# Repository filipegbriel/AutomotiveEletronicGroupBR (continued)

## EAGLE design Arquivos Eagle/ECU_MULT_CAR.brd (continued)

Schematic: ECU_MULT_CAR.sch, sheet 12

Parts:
BORBOLETA_1, BORBOLETA_2: PINO_TORNEADO
C38: 33nF; C0805
C40, C115: 100nF; C0805
C95: 47uF/25V; E2,5-7
PIN: CONCTOR_BOSCH; V23542-A1280-B300
R41: 10K; M0805
U$3: MC33186; HSOP-20-PIN

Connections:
+5V: R41.1; also elsewhere on the board
BORBOLETA_PIN_66: BORBOLETA_2.1, PIN.66, U$3.14 (OUT2), U$3.15 (OUT2_2)
BORBOLETA_PIN_80: BORBOLETA_1.1, PIN.80, U$3.6 (OUT1), U$3.7 (OUT1_2)
GND3: U$3.1 (AGND); also elsewhere on the board
IGND: C38.2, C40.2, C95.-, C115.2, PIN.28, U$3.10 (PGND_2), U$3.11 (PGND_3), U$3.12 (PGND_4), U$3.21A (EPAD); also elsewhere on the board
LINHA_15_PIN27: C40.1, C95.+, C115.1, U$3.4 (VBAT), U$3.5 (VBAT_2), U$3.16 (VBAT_3); also elsewhere on the board
unnamed: C38.1, U$3.17 (CP)
RA3_ADMISS_DI2__BORBO: U$3.13 (DI2); also elsewhere on the board
RB1_ADMISS_DI1_BORBO: U$3.18 (DI1); also elsewhere on the board
RB2_ADMISS_COD_BORBO: U$3.8 (COD); also elsewhere on the board
RB3_ADMISS_IN1_BORBO: U$3.3 (IN1); also elsewhere on the board
RB4_ADMISS_SF_BORBO: R41.2, U$3.2 (SF); also elsewhere on the board
RB5_ADMISS_IN2_BORBO: U$3.19 (IN2); also elsewhere on the board

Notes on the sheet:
Controle da Válvula Borboleta
Circuito Admissão
FACULDADE DE TECNOLOGIA DE SANTO ANDRÉ Rua Prefeito Justino Paixão, 150 - Centro Santo André - SP - CEP:09020-130 (11) 4437-2216
MARK 1

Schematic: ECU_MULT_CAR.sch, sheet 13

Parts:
C25, C26, C27, C28, C29, C30, C31, C32, C107, C108: 100nF; C0805
D5, D6, D14, D15: 1n4148; MINIMELF
IC6, IC7: LM358D; SO08
PIN: CONCTOR_BOSCH; V23542-A1280-B300
R25, R26, R27, R28, R29, R30: 10K; M0805
RA0_ADMISS_TPS_1, RA1_ADMISS_TPS_2: PINO_TORNEADO
TPS_1_IN, TPS_2_IN: PINO_TORNEADO

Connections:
+5V: D5.C, D6.C, D14.C, D15.C; also elsewhere on the board
GND3: C25.1, C27.1, C28.2, C29.2, C30.1, C32.1, C107.1, C108.2, IC6.4 (V-), IC7.4 (V-); also elsewhere on the board
unnamed: C107.2, D5.A, IC6.3 (+IN), R25.2
unnamed: IC6.1 (OUT), IC6.2 (-IN), R26.1
unnamed: C26.1, R26.2, R27.1
unnamed: C27.2, IC6.5 (+IN), R27.2
unnamed: C29.1, D6.A, IC7.3 (+IN), R28.2
unnamed: IC7.1 (OUT), IC7.2 (-IN), R29.1
unnamed: C31.1, R29.2, R30.1
unnamed: C32.2, IC7.5 (+IN), R30.2
RA0_ADMISS_TPS_1: C26.2, C28.1, D14.A, IC6.6 (-IN), IC6.7 (OUT), RA0_ADMISS_TPS_1.1; also elsewhere on the board
RA1_ADMISS_TPS_2: C31.2, C108.1, D15.A, IC7.6 (-IN), IC7.7 (OUT), RA1_ADMISS_TPS_2.1; also elsewhere on the board
TPS1_PIN_75: PIN.75, R25.1, TPS_1_IN.1
TPS2_PIN_68: PIN.68, R28.1, TPS_2_IN.1
V+: C25.2, C30.2, IC6.8 (V+), IC7.8 (V+); also elsewhere on the board

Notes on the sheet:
Circuito Condicionador Analógico Admissão
TPS_1
TPS_2
FACULDADE DE TECNOLOGIA DE SANTO ANDRÉ Rua Prefeito Justino Paixão, 150 - Centro Santo André - SP - CEP:09020-130 (11) 4437-2216
MARK 1

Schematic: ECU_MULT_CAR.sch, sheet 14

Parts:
BOB1, BOB2: LEDKA-3528ASYC; KA-3528ASYC
C39: 100uF/16V; E2,5-7
C72, C93, C100: 100pF; C0805
C89, C90: 22pF; C0805
JP3: JP3Q
LED3: LEDKA-3528ASYC; KA-3528ASYC
PIN: CONCTOR_BOSCH; V23542-A1280-B300
Q3: 10Mhz; SM49
R110, R146, R147: 1K; M0805
R116: 470R; M0805
R117: 10K; M0805
R145: 1M; M0805
S6: 10-XX; B3F-10XX
SINCRONISMO: PIC18F44K22; DIP40
SV2: MA03-1
X4, X6: MKDSN1,5/3-5,08

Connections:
+5V: C39.+, C72.1, C93.1, R110.2, R117.1, SINCRONISMO.11 (VCC), SINCRONISMO.32 (VCC_1); also elsewhere on the board
DGND: BOB1.C, BOB2.C, C39.-, C72.2, C89.1, C90.1, C93.2, C100.2, JP3.5, S6.1 (S), S6.2 (S1), SINCRONISMO.12 (GND), SINCRONISMO.31 (GND_1); also elsewhere on the board
ED_PIN_57: PIN.57, R147.1, SINCRONISMO.15 (RC0/P2B/T3CKI/T3G/T1CKI/SOSCO)
ED_PIN_71: PIN.71, R146.1, SINCRONISMO.16 (RC1/P2A/CCP2/SOSCI)
LINHA15: SINCRONISMO.34 (RB1/INT1/C12IN3-/AN10); also elsewhere on the board
unnamed: BOB1.A, R146.2
unnamed: BOB2.A, R147.2
unnamed: C89.2, Q3.1, R145.2, SINCRONISMO.13 (RA7/CLKI/OSC1)
unnamed: SINCRONISMO.2 (RA0/C12IN0-/ANO), X4.1
unnamed: LED3.A, R110.1
unnamed: C90.2, Q3.2, R145.1, SINCRONISMO.14 (RA6/CLKO/OSC2)
unnamed: LED3.C, SINCRONISMO.4 (RA2/C2IN+/AN2/DACOUT/VREF-), X6.2
unnamed: R116.2, SINCRONISMO.1 (~MCLR/VPP/RE3)
unnamed: C100.1, JP3.1, R116.1, R117.2, S6.3, S6.4 (P1)
unnamed: JP3.2, SINCRONISMO.40 (RB7/IOC3/PGD)
unnamed: JP3.3, SINCRONISMO.39 (RB6/IOC2/PGC)
unnamed: SINCRONISMO.3 (RA1/C12IN1-/AN1), X6.3
unnamed: SINCRONISMO.5 (RA3/C1IN+/AN3/VREF+), X6.1
RA4_SINCRO_BOM_PART_FRIA: SINCRONISMO.6 (RA4/C1OUT/SRQ/TOCKI); also elsewhere on the board
RB0_SINCRO_SELEC_ROTACAO_1: SINCRONISMO.33 (RB0/INT0/FLT0/SRI/AN12), SV2.1
RB0_SINCRO_SELEC_ROTACAO_2: SINCRONISMO.38 (RB5/IOC1/P3A/CCP3/T3CKI/T1G/AN13), SV2.3
RB2_SINCRO_INJ_PART_FRIA: SINCRONISMO.35 (RB2/INT32/CTED1/AN8); also elsewhere on the board
RB3_SINCRO_VENT_VEL_1: SINCRONISMO.36 (RB3/CTED2/P2A/CCP2/C12IN2-/AN9); also elsewhere on the board
RB4_SINCRO_VENT_VEL_2: SINCRONISMO.37 (RB4/IOC0/TG5/AN11); also elsewhere on the board
RC2_SINCRO_RELE_AR_COND: SINCRONISMO.17 (RC2/CTPLS/P1A/CCP1/T5CKI/AN14); also elsewhere on the board
RC6_GERENCI_RA5_CS_SINCRON: SINCRONISMO.7 (RA5/C2OUT/SRNQ/~SS1/HLVDIN/AN4); also elsewhere on the board
RC6_SINCRO_MAXI_IGN/INJ: SINCRONISMO.25 (RC6/TX1/CK1/AN18); also elsewhere on the board
RC7_SINCRO_NOMI_IGN/INJ: SINCRONISMO.26 (RC7/RX1/DT1/AN19); also elsewhere on the board
RD0_SINCRO_DIN0_IGN/INJ: SINCRONISMO.21 (RD2/P2B/AN22); also elsewhere on the board
RD1_SINCRO_DIN1_IGN/INJ: SINCRONISMO.22 (RD3/P2C/~SS2/AN23); also elsewhere on the board
RD2_SINCRO_DIN2_IGN/INJ: SINCRONISMO.19 (RD0/SCK2/SCL2/AN20); also elsewhere on the board
RD3_SINCRO_DIN3_IGN/INJ: SINCRONISMO.20 (RD1/CCP4/SDI2/SDA2/AN21); also elsewhere on the board
RD4_SINCRO_GIN0_IGN/INJ: SINCRONISMO.27 (RD4/P2D/SDO2/AN24); also elsewhere on the board
RD5_SINCRO_GIN1_IGN/INJ: SINCRONISMO.28 (RD5/P1B/AN25); also elsewhere on the board
RD6_SINCRO_GIN2_IGN/INJ: SINCRONISMO.29 (RD6/P1C/TX2/CK2/AN26); also elsewhere on the board
RD7_SINCRO_GIN3_IGN/INJ: SINCRONISMO.30 (RD7/P1D/RX2/DT2/AN27); also elsewhere on the board
RE0_SINCRO_OUT_EN_IGN/INJ: SINCRONISMO.8 (RE0/P3A/CCP3/AN5); also elsewhere on the board
RE1_SINCRO_SPK_IGN/INJ: SINCRONISMO.9 (RE1/P3B/AN6); also elsewhere on the board
RE2_SINCRO_FASE: SINCRONISMO.10 (RE2/CCP5/AN7); also elsewhere on the board
ROTAÇÃO: SV2.2; also elsewhere on the board
SCK1_GERENC: SINCRONISMO.18 (RC3/SCK1/SCL1/AN15); also elsewhere on the board
SDI1_GERENC: SINCRONISMO.24 (RC5/SDO1/AN17); also elsewhere on the board
SDO1_GERENC: SINCRONISMO.23 (RC4/SDI1/SDA1/AN16); also elsewhere on the board
SENSOR_COMBUSTIVEL: X4.2; also elsewhere on the board
SENSOR_VELOCIDADE: X4.3; also elsewhere on the board

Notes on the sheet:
PIC Sincronismo
FACULDADE DE TECNOLOGIA DE SANTO ANDRÉ Rua Prefeito Justino Paixão, 150 - Centro Santo André - SP - CEP:09020-130 (11) 4437-2216
MARK 1

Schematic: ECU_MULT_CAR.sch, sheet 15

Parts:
C41, C46, C47, C48, C49, C50, C62: 100nF; C0805
IGN1, IGN2, IGN3, IGN4: LEDKA-3528ASYC; KA-3528ASYC
INJ1, INJ2, INJ3, INJ4: LEDKA-3528ASYC; KA-3528ASYC
MC1: MC33810; SOIC_32_PIN
PIN: CONCTOR_BOSCH; V23542-A1280-B300
R42, R49, R50, R51: 36k/1W; R2512
R52, R53: 100R; M0805
R54: 0R02; M0805
R55, R56, R57, R58: 4K; M0805
R119, R120, R121, R122, R123, R124, R125, R126: 1K; M0805
R127, R128: 10K; M0805
U$4, U$6, U$7, U$8: IRGS14C40L; TO-263AB
X5: MKDSN1,5/4-5,08

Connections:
+5V: C48.1, MC1.8 (VDD), R127.2, R128.2; also elsewhere on the board
BOBINA_1: C41.1, R42.2, U$4.SOURCE (DRAIN), X5.1
BOBINA_2: C47.1, R49.2, U$6.SOURCE (DRAIN), X5.2
BOBINA_3: C46.1, R50.2, U$7.SOURCE (DRAIN), X5.3
BOBINA_4: C49.1, R51.2, U$8.SOURCE (DRAIN), X5.4
DGND: C48.2, C50.2, IGN1.C, IGN2.C, IGN3.C, IGN4.C, INJ1.C, INJ2.C, INJ3.C, INJ4.C; also elsewhere on the board
IGND: C62.2, MC1.33 (GND), R53.2, R54.1, R55.2, R56.2, R57.2, R58.2; also elsewhere on the board
INJETOR_1_PIN_79: MC1.1 (OUT0), PIN.79
INJETOR_2_PIN_59: MC1.16 (OUT1), PIN.59
INJETOR_3_PIN_73: MC1.32 (OUT2), PIN.73
INJETOR_4_PIN_65: MC1.17 (OUT3), PIN.65
unnamed: C41.2, MC1.2 (FB0), R42.1, R55.1
unnamed: C47.2, MC1.15 (FB1), R49.1, R56.1
unnamed: C46.2, MC1.31 (FB2), R50.1, R57.1
unnamed: C49.2, MC1.18 (FB3), R51.1, R58.1
unnamed: C62.1, R52.2, R54.2, U$4.DRAIN (SOURCE), U$6.DRAIN (SOURCE), U$7.DRAIN (SOURCE), U$8.DRAIN (SOURCE)
unnamed: MC1.3 (GD0), U$4.GATE
unnamed: MC1.14 (GD1), U$6.GATE
unnamed: MC1.30 (GD2), U$7.GATE
unnamed: MC1.19 (GD3), U$8.GATE
unnamed: MC1.26 (RSP), R52.1
unnamed: MC1.27 (RSN), R53.1
unnamed: INJ1.A, R119.2
unnamed: INJ2.A, R120.2
unnamed: INJ3.A, R121.2
unnamed: INJ4.A, R122.2
unnamed: IGN1.A, R123.2
unnamed: IGN2.A, R124.2
unnamed: IGN3.A, R125.2
unnamed: IGN4.A, R126.2
RC1_GERENC_CS_INJ/IGN: MC1.4 (/CS); also elsewhere on the board
RC6_SINCRO_MAXI_IGN/INJ: MC1.29 (MAXI); also elsewhere on the board
RC7_SINCRO_NOMI_IGN/INJ: MC1.28 (NOMI); also elsewhere on the board
RD0_SINCRO_DIN0_IGN/INJ: MC1.10 (DIN0), R119.1; also elsewhere on the board
RD1_SINCRO_DIN1_IGN/INJ: MC1.11 (DIN1), R120.1; also elsewhere on the board
RD2_SINCRO_DIN2_IGN/INJ: MC1.12 (DIN2), R121.1; also elsewhere on the board
RD3_SINCRO_DIN3_IGN/INJ: MC1.13 (DIN3), R122.1; also elsewhere on the board
RD4_SINCRO_GIN0_IGN/INJ: MC1.24 (GIN0), R123.1; also elsewhere on the board
RD5_SINCRO_GIN1_IGN/INJ: MC1.23 (GIN1), R124.1; also elsewhere on the board
RD6_SINCRO_GIN2_IGN/INJ: MC1.22 (GIN2), R125.1; also elsewhere on the board
RD7_SINCRO_GIN3_IGN/INJ: MC1.21 (GIN3), R126.1; also elsewhere on the board
RE0_SINCRO_OUT_EN_IGN/INJ: MC1.9 (/OUT_EN), R127.1; also elsewhere on the board
RE1_SINCRO_SPK_IGN/INJ: MC1.20 (/SPKDUR), R128.1; also elsewhere on the board
SCK1_GERENC: MC1.5 (SCLK); also elsewhere on the board
SDI1_GERENC: MC1.7 (SO); also elsewhere on the board
SDO1_GERENC: MC1.6 (SI); also elsewhere on the board
V+: C50.1, MC1.25 (VPWR); also elsewhere on the board

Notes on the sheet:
Condicionador Digital Injeção/Ignição Sincronismo
FACULDADE DE TECNOLOGIA DE SANTO ANDRÉ Rua Prefeito Justino Paixão, 150 - Centro Santo André - SP - CEP:09020-130 (11) 4437-2216
MARK 1

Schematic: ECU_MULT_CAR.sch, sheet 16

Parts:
ANTER_IN: PINO_TORNEADO
C5, C6, C7, C8, C109, C116, C117, C118, C120, C121: 100nF; C0805
D2, D16, D21, D22: 1n4148; MINIMELF
IC2, IC9: LM358D; SO08
MAP_IN: PINO_TORNEADO
MAP_OUT: PINO_TORNEADO
PIN: CONCTOR_BOSCH; V23542-A1280-B300
R5, R6, R7, R158, R159: 10K; M0805
R157: 3K6; M0805
R160: 1K; M0805
RA2_ADMISS_ALTERNADOR: PINO_TORNEADO
S2: 2P2T

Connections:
+5V: D2.C, D16.C, D21.C, D22.C; also elsewhere on the board
GND3: C5.2, C6.2, C8.2, C109.2, C117.2, C118.2, C120.1, C121.1, IC2.4 (V-), IC9.4 (V-), R160.1; also elsewhere on the board
MAP_PIN10: PIN.10, S2.3.1, S2.3.2
MAP_PIN70: PIN.70, S2.1.1, S2.1.2
unnamed: C109.1, D2.A, IC2.3 (+IN), R5.2
unnamed: IC2.1 (OUT), IC2.2 (-IN), R6.1
unnamed: C7.2, R6.2, R7.1
unnamed: C6.1, IC2.5 (+IN), R7.2
unnamed: MAP_IN.1, R5.1, S2.2.1, S2.2.2
unnamed: ANTER_IN.1, PIN.11, R157.1
unnamed: C117.1, D21.A, IC9.3 (+IN), R157.2, R160.2
unnamed: IC9.1 (OUT), IC9.2 (-IN), R158.1
unnamed: C116.1, R158.2, R159.1
unnamed: C120.2, IC9.5 (+IN), R159.2
RA2_ADMISS_ALTERNADOR: C116.2, C121.2, D22.A, IC9.6 (-IN), IC9.7 (OUT), RA2_ADMISS_ALTERNADOR.1; also elsewhere on the board
RE0_GERENC_MAP: C5.1, C7.1, D16.A, IC2.6 (-IN), IC2.7 (OUT), MAP_OUT.1; also elsewhere on the board
V+: C8.1, C118.1, IC2.8 (V+), IC9.8 (V+); also elsewhere on the board

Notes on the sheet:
MAP
Alternador
Condicionador Analógico
FACULDADE DE TECNOLOGIA DE SANTO ANDRÉ Rua Prefeito Justino Paixão, 150 - Centro Santo André - SP - CEP:09020-130 (11) 4437-2216
MARK 1

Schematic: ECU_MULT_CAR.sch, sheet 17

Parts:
C42, C43, C57, C61, C75, C76, C105, C106: 100nF; C0805
LED4: LEDKA-3528ASYC; KA-3528ASYC
LINHA15: PINO_TORNEADO
LINHA_15_IN: PINO_TORNEADO
MEDI_VELO_IN: PINO_TORNEADO
MEDI_VELO_OUT: PINO_TORNEADO
PIN: CONCTOR_BOSCH; V23542-A1280-B300
R31, R45, R70, R92: 5K6; M0805
R43, R44, R71, R72, R85, R86, R87, R88, R91, R93, R129, R130, R135, R136, R141, R142: 10K; M0805
R111: 1K; M0805
RD2_GERENC_FREIO_1: PINO_TORNEADO
RE2_SINCRO_FASE: PINO_TORNEADO
S1: 2P2T
SENSOR_FASE_IN: PINO_TORNEADO
SENSOR_IN1: PINO_TORNEADO
U1, U3: LM339; SOIC14N

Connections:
+5V: C42.1, C43.1, C61.1, C76.1, R43.1, R44.1, R72.1, R85.1, R86.1, R87.1, R91.1, R129.1, R135.1, R141.1, U1.3 (V+); also elsewhere on the board
DGND: C42.2, C43.2, C57.2, C61.2, C75.2, C76.2, C105.2, C106.2, LED4.C, R31.2, R45.2, R70.2, R88.2, R92.2, R130.2, R136.2, R142.2, U1.12 (V-); also elsewhere on the board
LINHA15: LINHA15.1, R91.2, U1.1 (OUT); also elsewhere on the board
LINHA_15_PIN4: PIN.4, S1.1.1, S1.1.2
LINHA_15_PIN27: PIN.27, S1.3.1, S1.3.2; also elsewhere on the board
unnamed: R87.2, R88.1, U3.10 (-IN)
unnamed: R70.1, R71.2, U3.5 (+IN)
unnamed: C57.1, PIN.23, R71.1, SENSOR_IN1.1
unnamed: R129.2, R130.1, U3.4 (-IN)
unnamed: R92.1, R93.2, U1.7 (+IN)
unnamed: LED4.A, R111.1
unnamed: C75.1, LINHA_15_IN.1, R93.1, R111.2, S1.2.1, S1.2.2
unnamed: C106.1, PIN.60, R44.2, R45.1, SENSOR_FASE_IN.1, U3.9 (+IN)
unnamed: R135.2, R136.1, U3.8 (-IN)
unnamed: R141.2, R142.1, U1.6 (-IN)
RD1_ADMISS_VELOCIDA: MEDI_VELO_OUT.1, R86.2, U3.13 (OUT); also elsewhere on the board
RD2_GERENC_FREIO_1: R72.2, RD2_GERENC_FREIO_1.1, U3.2 (OUT); also elsewhere on the board
RE2_SINCRO_FASE: R43.2, RE2_SINCRO_FASE.1, U3.14 (OUT); also elsewhere on the board
SENSOR_VELOCIDADE: C105.1, MEDI_VELO_IN.1, PIN.5, R31.1, R85.2, U3.11 (+IN); also elsewhere on the board

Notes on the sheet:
Fase
Freio 1
Linha 15
Velocidade
Condicionador Digital
FACULDADE DE TECNOLOGIA DE SANTO ANDRÉ Rua Prefeito Justino Paixão, 150 - Centro Santo André - SP - CEP:09020-130 (11) 4437-2216
MARK 1

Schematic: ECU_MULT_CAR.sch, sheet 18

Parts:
C33: 330nF; C0805
C34: 47nF; C0805
C35: 1nF; C0805
C36, C37: 100nF; C0805
OP.MODE: M251
PIN: CONCTOR_BOSCH; V23542-A1280-B300
R33: 100K; M0805
R34: 1K; M0805
R35: 150K; M0805
R36, R39: 5K6; M0805
R37: 18K; M0805
R38, R40, R143, R144, R170: 10K; M0805
RELUTÂNCIA: PINO_TORNEADO
ROT_ANAL: PINO_TORNEADO
ROT_DIG_IN: PINO_TORNEADO
ROT_DIG_OUT: PINO_TORNEADO
SENSIBILIDADE: M251
SV3: MA04-2
U3: LM339; SOIC14N
U$2: LM1815; SOICLM1815

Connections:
+5V: C37.1, R35.1, R36.1, R38.1, R143.1, R170.1, SENSIBILIDADE.1 (O), U3.3 (V+), U$2.8 (VCC); also elsewhere on the board
DGND: C33.2, C34.2, C35.1, C36.2, C37.2, OP.MODE.3 (S), R33.1, R34.1, R39.2, R144.2, SENSIBILIDADE.3 (S), U3.12 (V-), U$2.2 (GND); also elsewhere on the board
ENTRADA_DIGITAL_PIN_53: PIN.53, SV3.2, SV3.8
unnamed: C33.1, R33.2, U$2.7 (PEAK)
unnamed: R37.1, U$2.3 (VIN)
unnamed: R34.2, U$2.10 (GATED)
unnamed: C35.2, OP.MODE.2, R35.2, U$2.14 (RC_TIMING)
unnamed: R39.1, R40.2, U3.7 (+IN)
unnamed: C36.1, R40.1, R170.2, ROT_DIG_IN.1, SV3.1
unnamed: SENSIBILIDADE.2, U$2.5 (MODE)
unnamed: R143.2, R144.1, U3.6 (-IN)
RELUTÂNCIA: C34.1, R37.2, RELUTÂNCIA.1, SV3.7
ROTAÇÃO: SV3.3, SV3.5; also elsewhere on the board
ROT_ANA: R36.2, ROT_ANAL.1, SV3.6, U$2.12 (PULSE_OUT)
ROT_DIG: R38.2, ROT_DIG_OUT.1, SV3.4, U3.1 (OUT)

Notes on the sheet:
Condicionador Analógico/Digital Rotação
FACULDADE DE TECNOLOGIA DE SANTO ANDRÉ Rua Prefeito Justino Paixão, 150 - Centro Santo André - SP - CEP:09020-130 (11) 4437-2216
MARK 1

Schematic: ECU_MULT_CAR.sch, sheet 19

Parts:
PIN: CONCTOR_BOSCH; V23542-A1280-B300
R32, R106, R155: 1K; M0805
R94, R96, R98, R100, R102, R148, R149, R150, R151: 100k; M0805
R95, R97, R99, R101, R103: 1k; M0805
R153: 220R; M0805
U$1, U$13, U$16, U$17, U$26, U$27, U$28, U$29, U$30: IRLL014N; SOT-223

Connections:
AQUECE_SONDA_PIN13: PIN.13, U$1.2 (D), U$1.4 (D)
AQUECE_SONDA_PIN_1: PIN.1, U$16.2 (D), U$16.4 (D)
BOMBA_PARTIDA_FRIO_PIN48: PIN.48, U$27.2 (D), U$27.4 (D)
CARVAO_ATIVO_PIN14: PIN.14, U$13.2 (D), U$13.4 (D)
DGND: R94.1, R96.1, R98.1, R100.1, R102.1, R148.1, R149.1, R150.1, R151.1, U$1.3 (S), U$13.3 (S), U$16.3 (S), U$17.3 (S), U$26.3 (S), U$27.3 (S), U$28.3 (S), U$29.3 (S), U$30.3 (S); also elsewhere on the board
INJETOR_PART_FRIO_PIN_64: PIN.64, U$26.2 (D), U$26.4 (D)
unnamed: R95.1, R98.2, U$16.1 (G)
unnamed: R96.2, R97.1, U$1.1 (G)
unnamed: R94.2, R99.1, U$13.1 (G)
unnamed: R100.2, R103.1, U$17.1 (G)
unnamed: R32.1, R148.2, U$26.1 (G)
unnamed: R106.1, R149.2, U$27.1 (G)
unnamed: R101.1, R102.2, U$30.1 (G)
unnamed: R150.2, R153.1, U$29.1 (G)
unnamed: R151.2, R155.1, U$28.1 (G)
RA4_SINCRO_BOM_PART_FRIA: R106.2; also elsewhere on the board
RB2_SINCRO_INJ_PART_FRIA: R32.2; also elsewhere on the board
RB3_SINCRO_VENT_VEL_1: R153.2; also elsewhere on the board
RB4_SINCRO_VENT_VEL_2: R101.2; also elsewhere on the board
RC2_SINCRO_RELE_AR_COND: R155.2; also elsewhere on the board
RD6_ADMISS_AQUEC_SONDA_1: R95.2; also elsewhere on the board
RD7_ADMISS_AQUEC_SONDA_2: R97.2; also elsewhere on the board
RD7_GERENC_BOMB_INJ: R103.2; also elsewhere on the board
RE2_ADMISS_CARVãO: R99.2; also elsewhere on the board
RELE_AR_CONDICIONADO_PIN42: PIN.42, U$28.2 (D), U$28.4 (D)
RELÉ5_BOMBA_INJET_PIN26: PIN.26, U$17.2 (D), U$17.4 (D)
VENTILADOR_VEL_1_PIN22: PIN.22, U$29.2 (D), U$29.4 (D)
VENTILADOR_VEL_2_PIN40: PIN.40, U$30.2 (D), U$30.4 (D)

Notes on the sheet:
Circuitos Condicionadores de Acionamento de Relés
FACULDADE DE TECNOLOGIA DE SANTO ANDRÉ Rua Prefeito Justino Paixão, 150 - Centro Santo André - SP - CEP:09020-130 (11) 4437-2216
MARK 1

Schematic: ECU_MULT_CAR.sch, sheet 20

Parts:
PIN: CONCTOR_BOSCH; V23542-A1280-B300

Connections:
+5V: PIN.6, PIN.8, PIN.55, PIN.62; also elsewhere on the board
+VBAT: PIN.15; also elsewhere on the board
DGND: PIN.2, PIN.67; also elsewhere on the board
GND3: PIN.7, PIN.19, PIN.54, PIN.61; also elsewhere on the board

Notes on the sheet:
Referência Negativa Analógica
Referência Negativa Ignição
Referência Negativa Digital
Pinos que não foram usados
Alimentação 12 Volts Bateria do Veiculo
Alimentação 5 Volts retificada
Informações
FACULDADE DE TECNOLOGIA DE SANTO ANDRÉ Rua Prefeito Justino Paixão, 150 - Centro Santo André - SP - CEP:09020-130 (11) 4437-2216
MARK 1

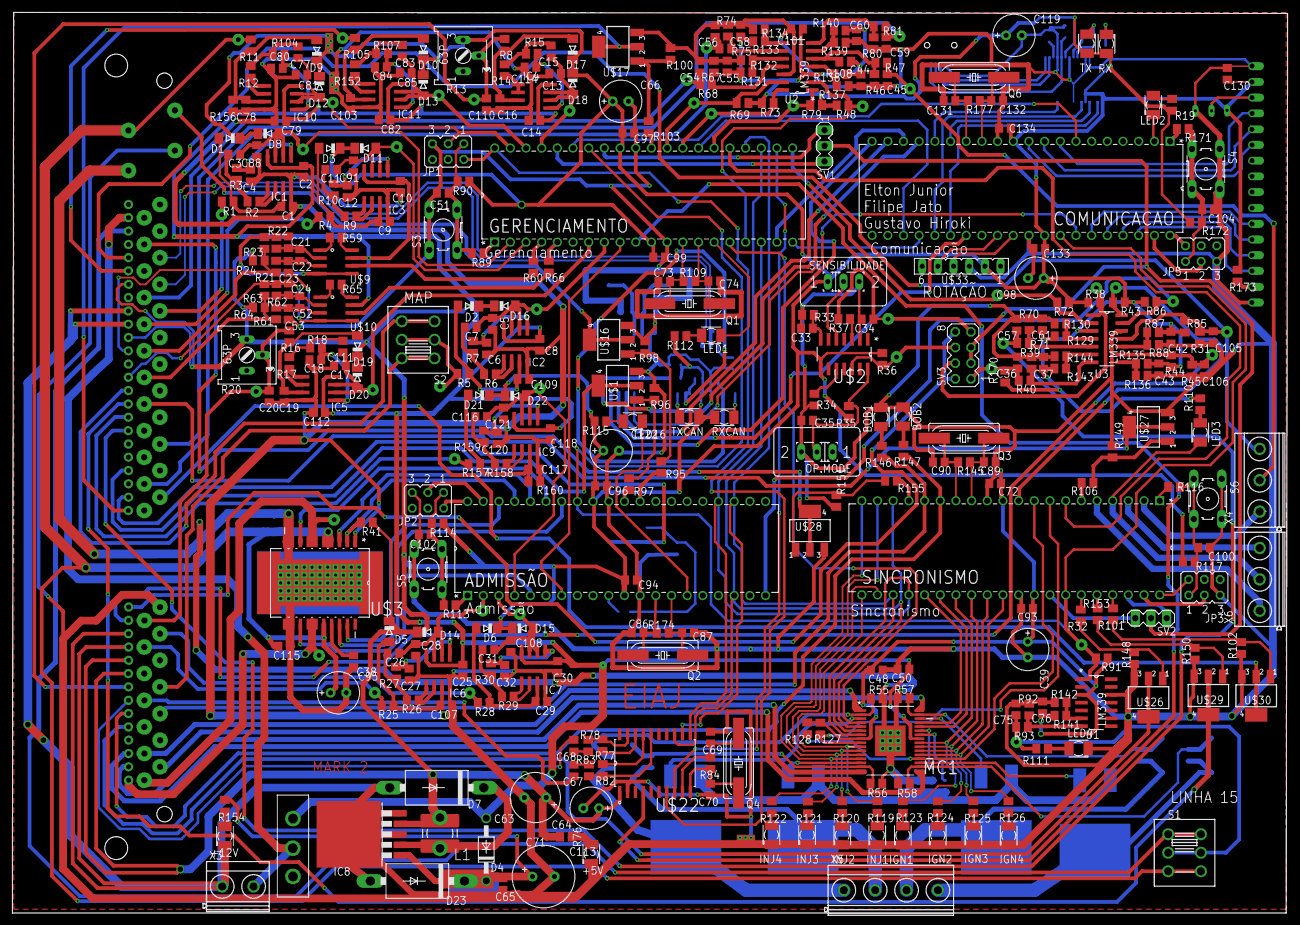
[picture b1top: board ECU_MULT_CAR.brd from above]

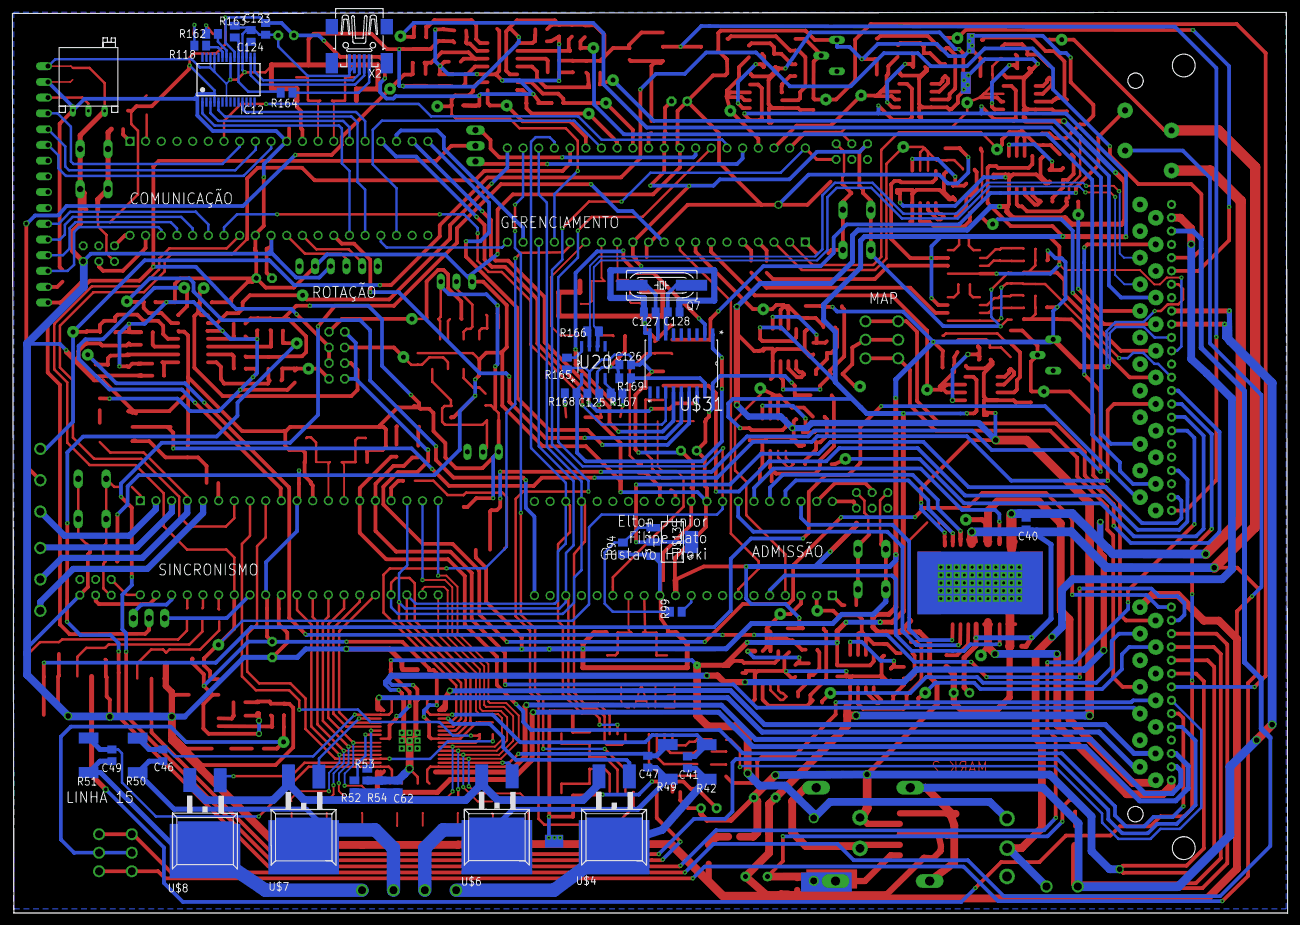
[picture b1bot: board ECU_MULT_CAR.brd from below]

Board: 2 copper layers, 206.6 x 145.9 mm, 466 parts (41 on the bottom side), 311 nets.

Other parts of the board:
DRILEGEND: DRILEGEND
U$14: A4L-LOC

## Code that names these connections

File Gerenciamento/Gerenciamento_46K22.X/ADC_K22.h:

/* 
 * File:   ADC_K22.h
 * Author: Hiroki
 *
 * Created on 1 de Maio de 2016, 00:18
 */

#ifndef ADC_K22_H
#define	ADC_K22_H

#include "Config_XC8.h"

/*_____________________TABELA DE ADC_________________________*/

#define AN_0	0b00000		//(pin 2    RA0)
#define AN_1	0b00001		//(pin 3    RA1)
#define AN_2	0b00010		//(pin 4    RA2)
#define AN_3	0b00011		//(pin 5    RA3)
#define AN_4	0b00100		//(pin 7    RA5)
#define AN_5	0b00101		//(pin 8    RE0)
#define AN_6	0b00110		//(pin 9    RE1)
#define AN_7	0b00111		//(pin 10   RE2)
#define AN_8	0b01000		//(pin 35   RB2)
#define AN_9	0b01001		//(pin 36   RB3)
#define AN_10	0b01010		//(pin 34   RB1)
#define AN_11	0b01011		//(pin 37   RB4)
#define AN_12	0b01100		//(pin 33   RB0)
#define AN_13	0b01101		//(pin 38   RB5)
#define AN_14	0b01110		//(pin 17   RC2)
#define AN_15	0b01111		//(pin 18   RC3)
#define AN_16	0b10000		//(pin 23   RC4)
#define AN_17	0b10001		//(pin 24   RC5)
#define AN_18	0b10010		//(pin 25   RC6)
#define AN_19	0b10011		//(pin 26   RC7)
#define AN_20	0b10100		//(pin 19   RD0)
#define AN_21	0b10101		//(pin 20   RD1)
#define AN_22	0b10110		//(pin 21   RD2)
#define AN_23	0b10111		//(pin 22   RD3)
#define AN_24	0b11000		//(pin 27   RD4)
#define AN_25	0b11001		//(pin 28   RD5)
#define AN_26	0b11010		//(pin 29   RD6)
#define AN_27	0b11011		//(pin 30   RD7)

#define nENABLE        1
#define nDISABLE       0
#define ON             1
#define OFF            0

#define REQ_ADC        ADCON0bits.ADON

#define Enable_ADC(value)   (value = ON)
#define Disable_ADC(value)  (value = OFF)
/*________________________________________________________________*/

#ifdef	__cplusplus
extern "C" {
#endif

    extern void Config_ADC( void );
    
    extern unsigned int Read_ADC(unsigned char channel);

#ifdef	__cplusplus
}
#endif

#endif	/* ADC_K22_H */

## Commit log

2018-07-10 Arquivos eagle
    Arquivos que geram a placa no software Eagle.
2018-07-10 Software atual
    v2.6
2018-07-10 Software
    V2.6
2018-08-13 organizando
    ...
2018-08-13 Testes
    aquivos guia para testes
2018-08-22 Relatórios
    22/08
2018-10-11 Resumos
